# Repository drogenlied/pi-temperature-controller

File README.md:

# Pi temperature controller
A Raspberry Pi based H-bridge controller designed to stabilize temperatures in an optics lab

## Hardware
  * Raspberry Pi (Model 2 recommended)
  * Measurement Specialities TSYS01 temperature sensor
  * Adum 14xx isolators between control and driver
  * VNH3SP30 H-bridge driver for output
  
## Features
  * Can control Peltier elements as well as resistive heaters for temperature stabilisation.
  * Fabrication should be possible in every university PCB shop
  * Hand soldering is possible but reflowing the VNH3SP30 is recommended
  
## Software
Test software is in this repository but https://github.com/Ulm-IQO/qudi is recommended for operation.

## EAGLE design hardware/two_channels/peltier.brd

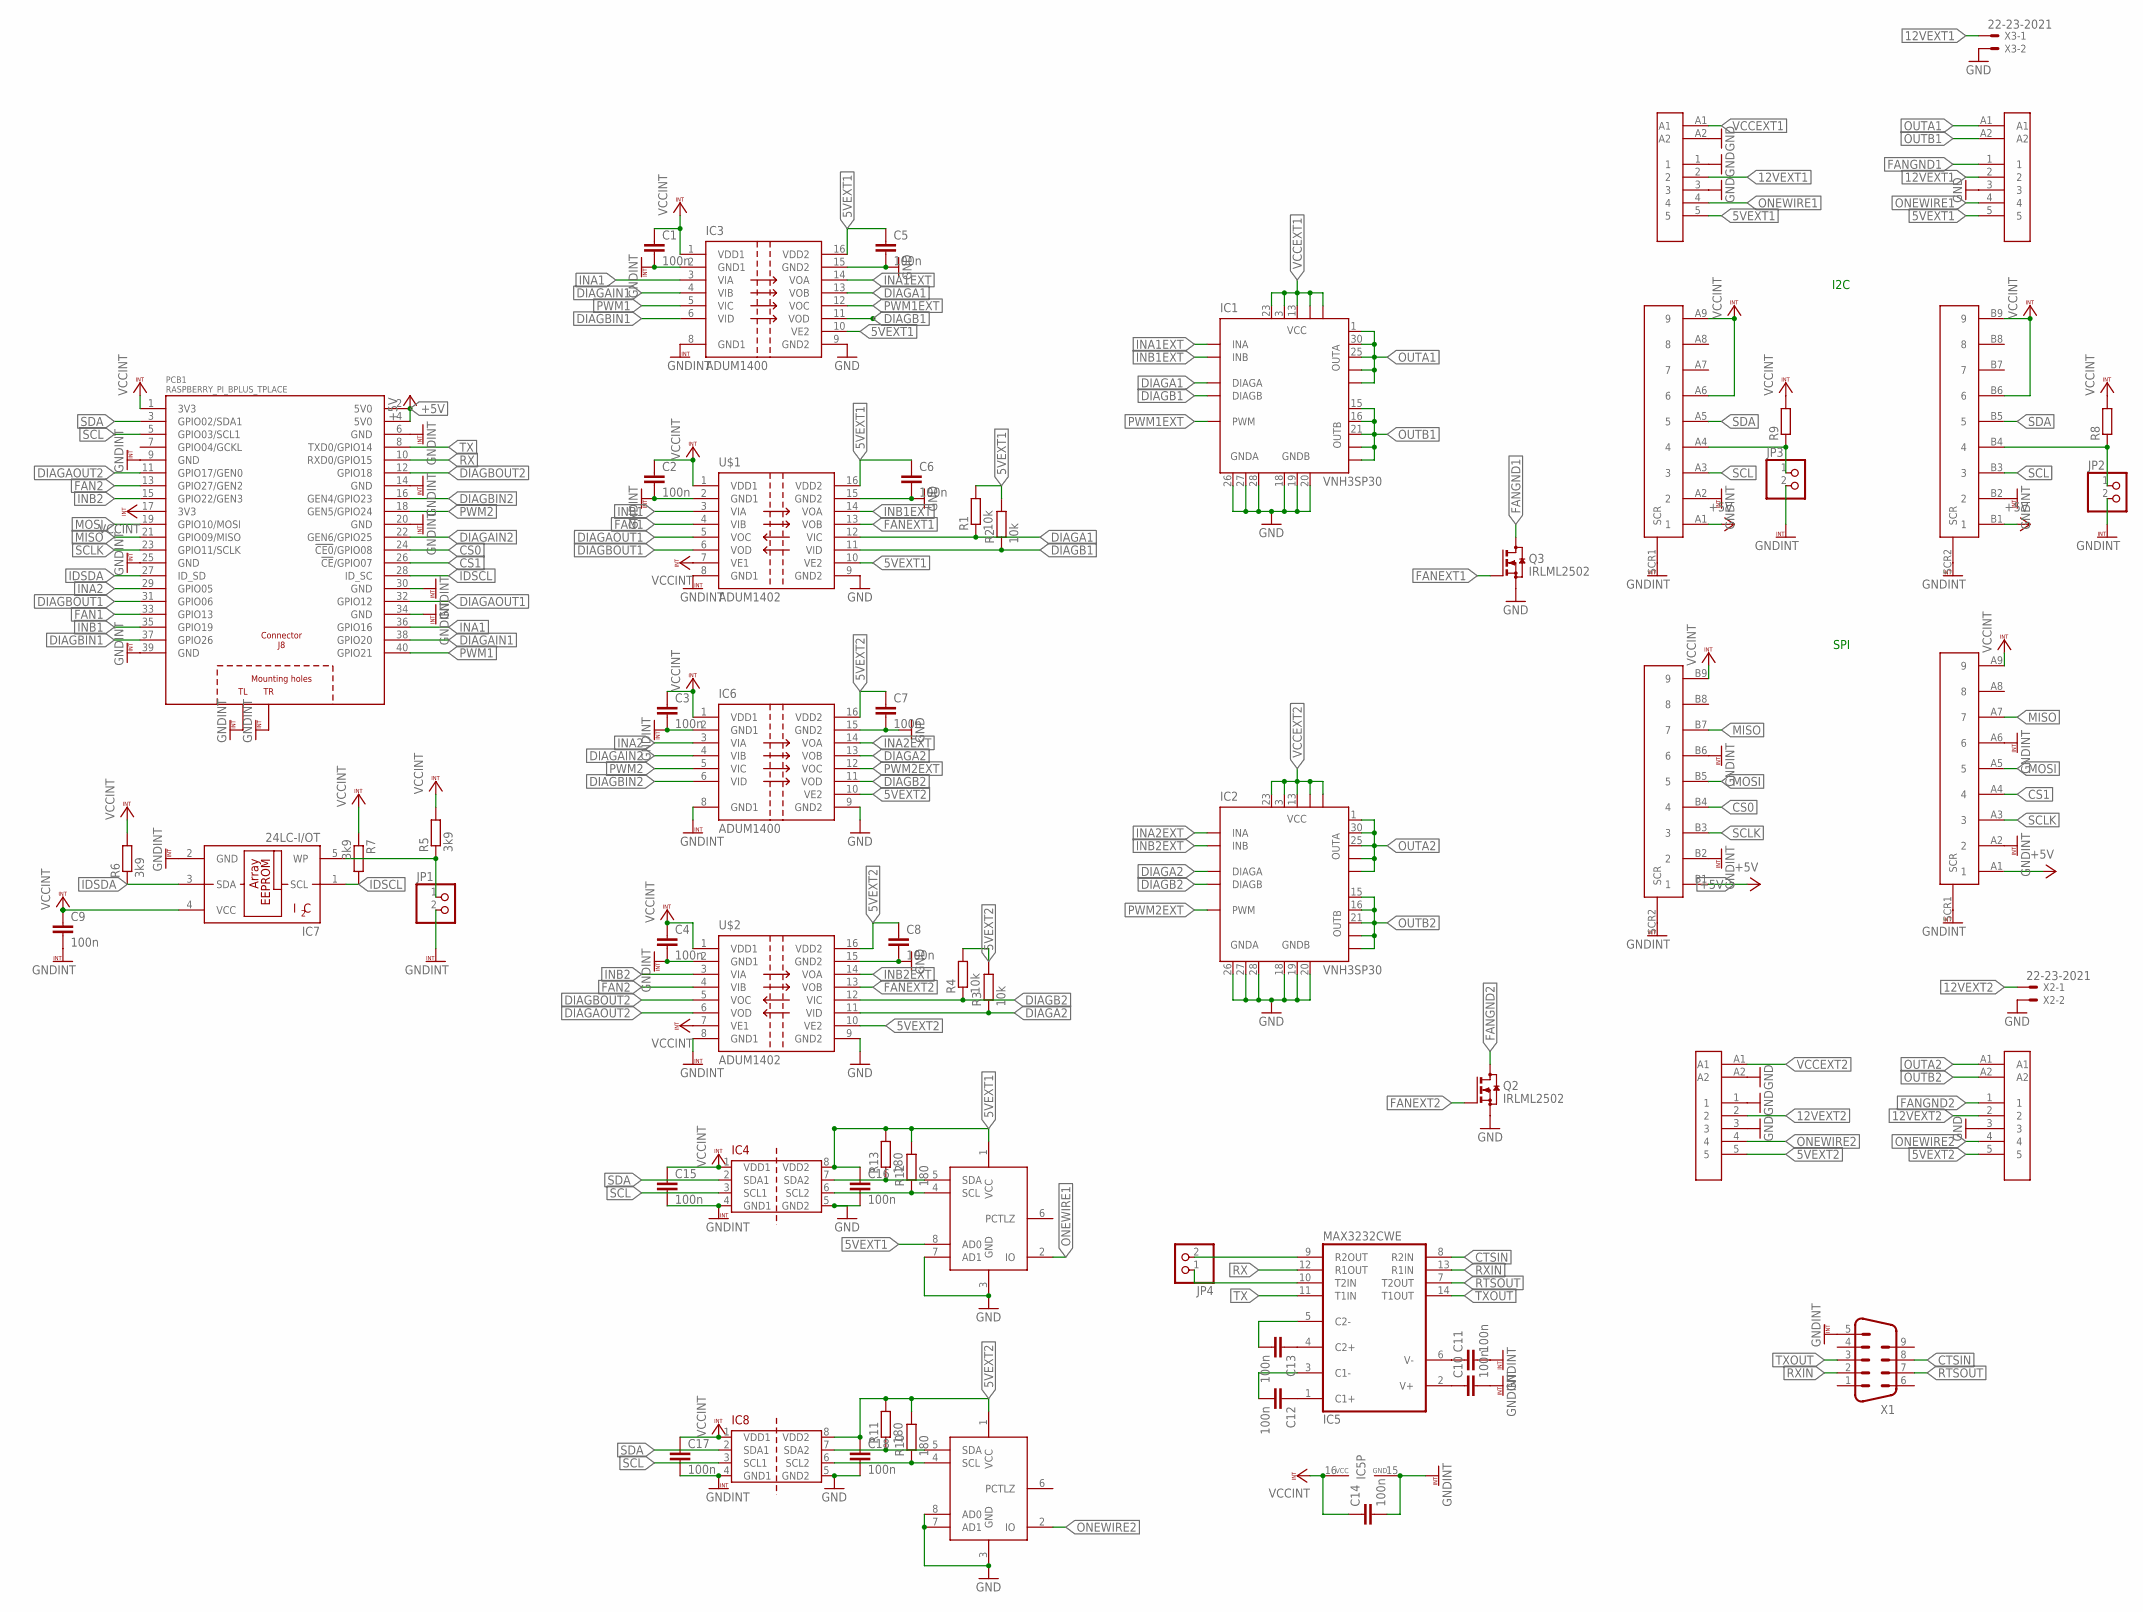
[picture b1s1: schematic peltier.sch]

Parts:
C1, C2, C3, C4, C5, C6, C7, C8, C9, C10, C11, C12, C13, C14, C15, C16, C17, C18: 100n; C0805
IC1, IC2: VNH3SP30; MULTIPOWERSO-30
IC3, IC6: ADUM1400; SO16W
IC4, IC8: ADUM1250; SO08
IC5: MAX3232CWE; SO16L
IC7: 24LC-I/OT; SOT23-5
JP1, JP2, JP3, JP4: PINHD-1X2; 1X02
PCB1: RASPBERRY_PI_BPLUS_TPLACE
Q2, Q3: IRLML2502; SOT23
R1, R2, R3, R4: 10k; R0805
R5, R6, R7: 3k9; R0805
R8, R9: R-EU_R0805; R0805
R10, R11, R12, R13: 180; R0805
U$1, U$2: ADUM1402; SO16W
U$3, U$4: 7W2-F
U$5, U$6: 7W2-M
U$11, U$12: 164A19919X
U$14, U$15: DS2483-100; SO-08
X1: M09HP
X2, X3: 22-23-2021

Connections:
5VEXT1: C5.1, C6.1, C16.1, IC3.10 (VE2), IC3.16 (VDD2), IC4.8 (VDD2), R1.2, R2.2, R12.2, R13.2, U$1.10 (VE2), U$1.16 (VDD2), U$3.5, U$5.5, U$14.1 (VCC), U$14.8 (AD0)
5VEXT2: C7.1, C8.1, C18.1, IC6.10 (VE2), IC6.16 (VDD2), IC8.8 (VDD2), R3.2, R4.2, R10.2, R11.2, U$2.10 (VE2), U$2.16 (VDD2), U$4.5, U$6.5, U$15.1 (VCC)
12VEXT1: U$3.2, U$5.2, X3.1
12VEXT2: U$4.2, U$6.2, X2.1
+5V: PCB1.2 (5V0), PCB1.4 (5V0), U$11.A1 (1), U$11.B1 (1), U$12.A1 (1), U$12.B1 (1)
CS0: PCB1.24 (!CE0!/GPIO08), U$12.B4 (4)
CS1: PCB1.26 (!CE!/GPIO07), U$12.A4 (4)
CTSIN: IC5.8 (R2IN), X1.8
DIAGA1: IC1.6 (DIAGA), IC3.13 (VOB), R1.1, U$1.12 (VIC)
DIAGA2: IC2.6 (DIAGA), IC6.13 (VOB), R3.1, U$2.11 (VID)
DIAGAIN1: IC3.4 (VIB), PCB1.38 (GPIO20)
DIAGAIN2: IC6.4 (VIB), PCB1.22 (GEN6/GPIO25)
DIAGAOUT1: PCB1.32 (GPIO12), U$1.5 (VOC)
DIAGAOUT2: PCB1.11 (GPIO17/GEN0), U$2.6 (VOD)
DIAGB1: IC1.10 (DIAGB), IC3.11 (VOD), R2.1, U$1.11 (VID)
DIAGB2: IC2.10 (DIAGB), IC6.11 (VOD), R4.1, U$2.12 (VIC)
DIAGBIN1: IC3.6 (VID), PCB1.37 (GPIO26)
DIAGBIN2: IC6.6 (VID), PCB1.16 (GEN4/GPIO23)
DIAGBOUT1: PCB1.31 (GPIO06), U$1.6 (VOD)
DIAGBOUT2: PCB1.12 (GPIO18), U$2.5 (VOC)
FAN1: PCB1.33 (GPIO13), U$1.4 (VIB)
FAN2: PCB1.13 (GPIO27/GEN2), U$2.4 (VIB)
FANEXT1: Q3.1 (G), U$1.13 (VOB)
FANEXT2: Q2.1 (G), U$2.13 (VOB)
FANGND1: Q3.3 (D), U$3.1
FANGND2: Q2.3 (D), U$4.1
GND: C5.2, C6.2, C7.2, C8.2, C16.2, C18.2, IC1.18 (GNDB), IC1.19 (GNDB), IC1.20 (GNDB), IC1.26 (GNDA), IC1.27 (GNDA), IC1.28 (GNDA), IC2.18 (GNDB), IC2.19 (GNDB), IC2.20 (GNDB), IC2.26 (GNDA), IC2.27 (GNDA), IC2.28 (GNDA), IC3.9 (GND2), IC3.15 (GND2), IC4.5 (GND2), IC6.9 (GND2), IC6.15 (GND2), IC8.5 (GND2), Q2.2 (S), Q3.2 (S), U$1.9 (GND2), U$1.15 (GND2), U$2.9 (GND2), U$2.15 (GND2), U$3.3, U$4.3, U$5.1, U$5.3, U$5.A2, U$6.1, U$6.3, U$6.A2, U$14.3 (GND), U$14.7 (AD1), U$15.3 (GND), U$15.7 (AD1), U$15.8 (AD0), X2.2, X3.2
GNDINT: C1.2, C2.2, C3.2, C4.2, C9.2, C10.2, C11.2, C14.2, C15.2, C17.2, IC3.2 (GND1), IC3.8 (GND1), IC4.4 (GND1), IC5.15 (GND), IC6.2 (GND1), IC6.8 (GND1), IC7.2 (GND), IC8.4 (GND1), JP1.2, JP2.2, JP3.2, PCB1.6 (GND), PCB1.9 (GND), PCB1.14 (GND), PCB1.20 (GND), PCB1.25 (GND), PCB1.30 (GND), PCB1.34 (GND), PCB1.39 (GND), PCB1.PE_TL (TL), PCB1.PE_TR (TR), U$1.2 (GND1), U$1.8 (GND1), U$2.2 (GND1), U$2.8 (GND1), U$11.A2 (2), U$11.B2 (2), U$11.SCR1 (SCR), U$11.SCR2 (SCR), U$12.A2 (2), U$12.A6 (6), U$12.B2 (2), U$12.B6 (6), U$12.SCR1 (SCR), U$12.SCR2 (SCR), X1.5
IDSCL: IC7.1 (SCL), PCB1.28 (ID_SC), R7.2
IDSDA: IC7.3 (SDA), PCB1.27 (ID_SD), R6.1
INA1: IC3.3 (VIA), PCB1.36 (GPIO16)
INA1EXT: IC1.5 (INA), IC3.14 (VOA)
INA2: IC6.3 (VIA), PCB1.29 (GPIO05)
INA2EXT: IC2.5 (INA), IC6.14 (VOA)
INB1: PCB1.35 (GPIO19), U$1.3 (VIA)
INB1EXT: IC1.11 (INB), U$1.14 (VOA)
INB2: PCB1.15 (GPIO22/GEN3), U$2.3 (VIA)
INB2EXT: IC2.11 (INB), U$2.14 (VOA)
MISO: PCB1.21 (GPIO09/MISO), U$12.A7 (7), U$12.B7 (7)
MOSI: PCB1.19 (GPIO10/MOSI), U$12.A5 (5), U$12.B5 (5)
unnamed: IC7.5 (WP), JP1.1, R5.1
unnamed: JP3.1, R9.1, U$11.A4 (4)
unnamed: JP2.1, R8.1, U$11.B4 (4)
unnamed: C10.1, IC5.2 (V+)
unnamed: C11.1, IC5.6 (V-)
unnamed: C12.1, IC5.1 (C1+)
unnamed: C12.2, IC5.3 (C1-)
unnamed: C13.1, IC5.4 (C2+)
unnamed: C13.2, IC5.5 (C2-)
unnamed: IC5.9 (R2OUT), JP4.2
unnamed: IC5.10 (T2IN), JP4.1
unnamed: IC4.7 (SDA2), R13.1, U$14.5 (SDA)
unnamed: IC4.6 (SCL2), R12.1, U$14.4 (SCL)
unnamed: IC8.7 (SDA2), R11.1, U$15.5 (SDA)
unnamed: IC8.6 (SCL2), R10.1, U$15.4 (SCL)
ONEWIRE1: U$3.4, U$5.4, U$14.2 (IO)
ONEWIRE2: U$4.4, U$6.4, U$15.2 (IO)
OUTA1: IC1.1 (OUTA), IC1.25 (OUTA), IC1.30 (OUTA), IC1.OUTA, IC1.OUTA@1 (OUTA), U$3.A1
OUTA2: IC2.1 (OUTA), IC2.25 (OUTA), IC2.30 (OUTA), IC2.OUTA, IC2.OUTA@1 (OUTA), U$4.A1
OUTB1: IC1.15 (OUTB), IC1.16 (OUTB), IC1.21 (OUTB), IC1.OUTB, IC1.OUTB@1 (OUTB), U$3.A2
OUTB2: IC2.15 (OUTB), IC2.16 (OUTB), IC2.21 (OUTB), IC2.OUTB, IC2.OUTB@1 (OUTB), U$4.A2
PWM1: IC3.5 (VIC), PCB1.40 (GPIO21)
PWM1EXT: IC1.8 (PWM), IC3.12 (VOC)
PWM2: IC6.5 (VIC), PCB1.18 (GEN5/GPIO24)
PWM2EXT: IC2.8 (PWM), IC6.12 (VOC)
RTSOUT: IC5.7 (T2OUT), X1.7
RX: IC5.12 (R1OUT), PCB1.10 (RXD0/GPIO15)
RXIN: IC5.13 (R1IN), X1.2
SCL: IC4.3 (SCL1), IC8.3 (SCL1), PCB1.5 (GPIO03/SCL1), U$11.A3 (3), U$11.B3 (3)
SCLK: PCB1.23 (GPIO11/SCLK), U$12.A3 (3), U$12.B3 (3)
SDA: IC4.2 (SDA1), IC8.2 (SDA1), PCB1.3 (GPIO02/SDA1), U$11.A5 (5), U$11.B5 (5)
TX: IC5.11 (T1IN), PCB1.8 (TXD0/GPIO14)
TXOUT: IC5.14 (T1OUT), X1.3
VCCEXT1: IC1.3 (VCC), IC1.13 (VCC), IC1.23 (VCC), IC1.VCC, IC1.VCC@1 (VCC), U$5.A1
VCCEXT2: IC2.3 (VCC), IC2.13 (VCC), IC2.23 (VCC), IC2.VCC, IC2.VCC@1 (VCC), U$6.A1
VCCINT: C1.1, C2.1, C3.1, C4.1, C9.1, C14.1, C15.1, C17.1, IC3.1 (VDD1), IC4.1 (VDD1), IC5.16 (VCC), IC6.1 (VDD1), IC7.4 (VCC), IC8.1 (VDD1), PCB1.1 (3V3), PCB1.17 (3V3), R5.2, R6.2, R7.1, R8.2, R9.2, U$1.1 (VDD1), U$1.7 (VE1), U$2.1 (VDD1), U$2.7 (VE1), U$11.A6 (6), U$11.A9 (9), U$11.B6 (6), U$11.B9 (9), U$12.A9 (9), U$12.B9 (9)

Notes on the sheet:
I2C
SPI

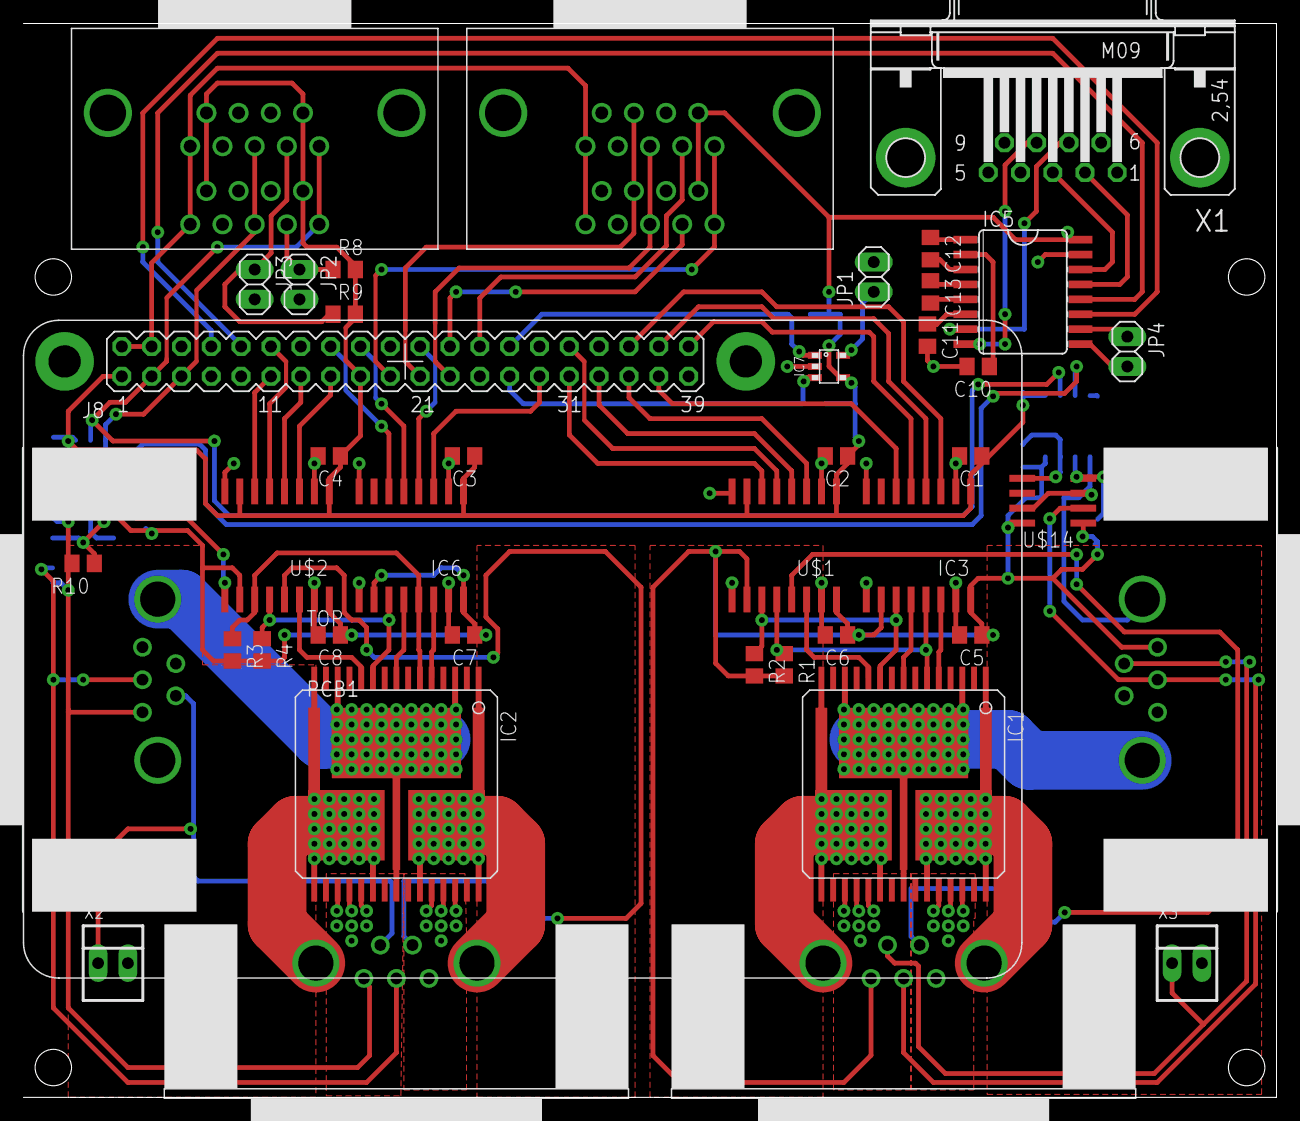
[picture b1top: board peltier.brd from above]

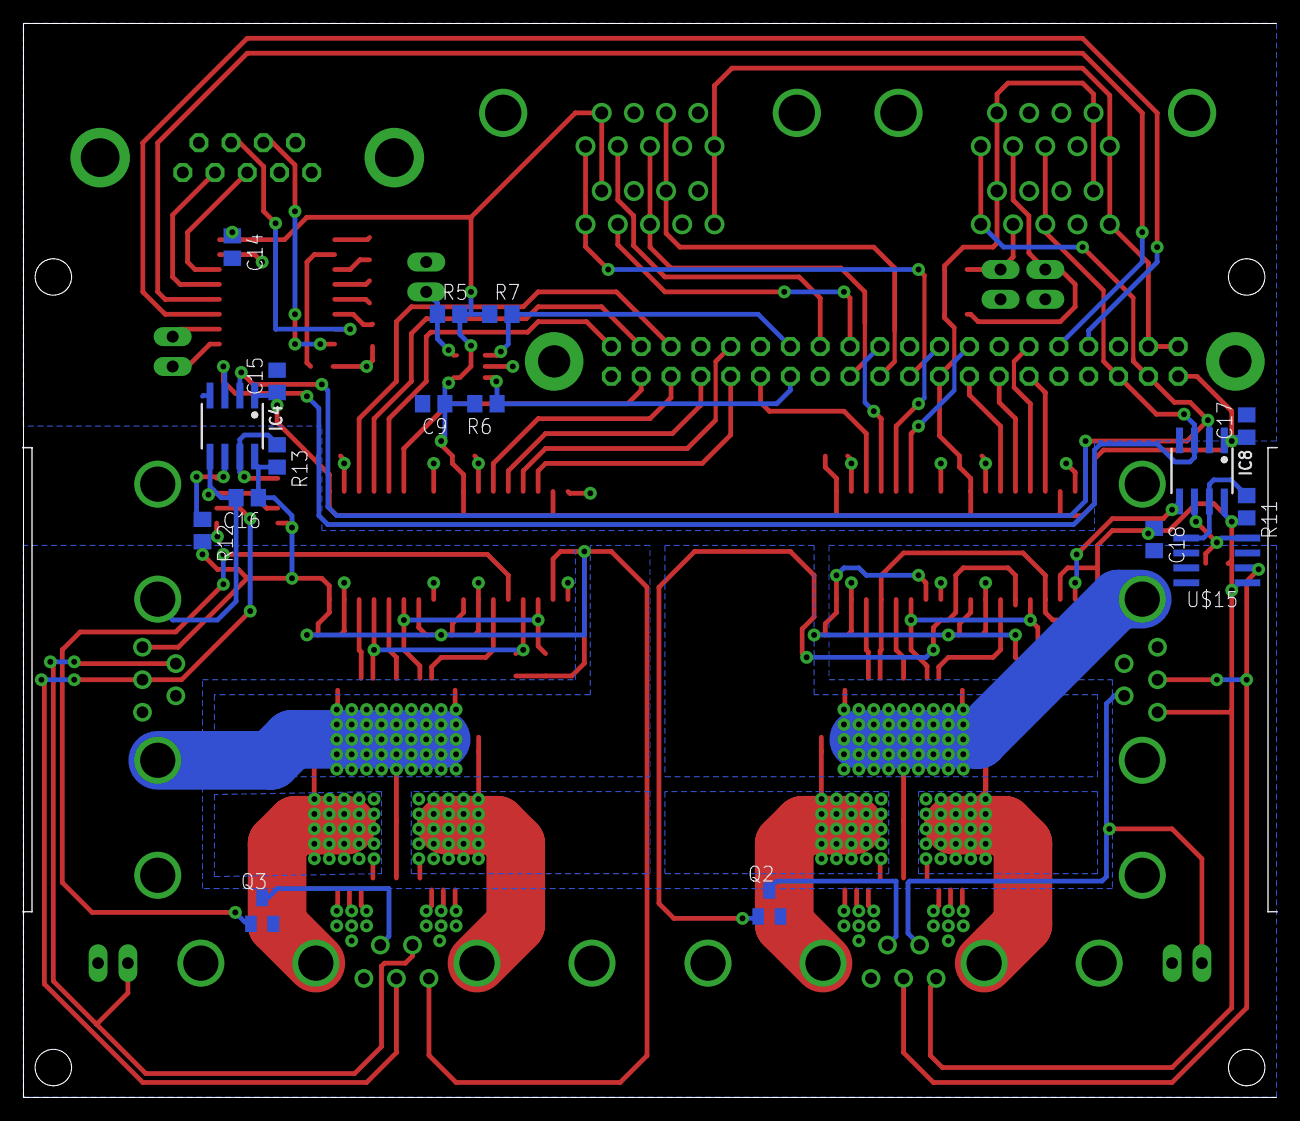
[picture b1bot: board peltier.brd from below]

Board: 2 copper layers, 106.7 x 91.4 mm, 59 parts (17 on the bottom side), 76 nets.

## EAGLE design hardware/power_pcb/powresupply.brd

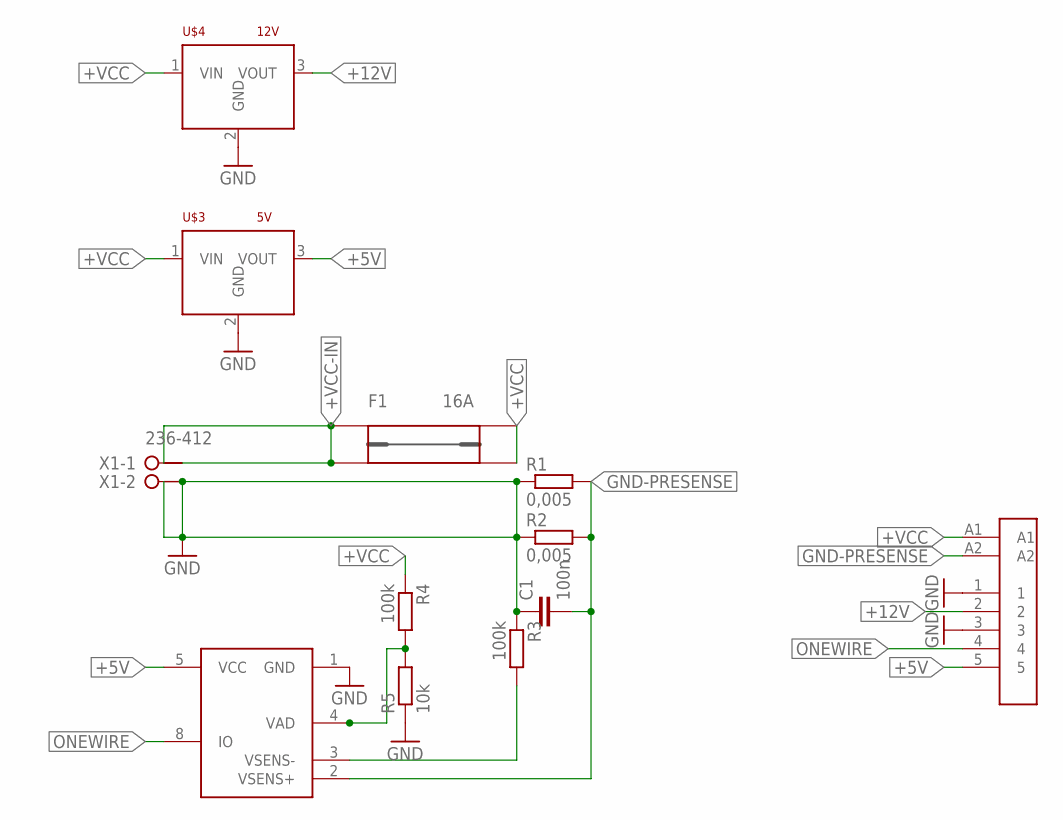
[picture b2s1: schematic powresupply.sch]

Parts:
C1: 100n; C0805
F1: 16A; 1A3400
R1, R2: 0,005; R2512
R3, R4: 100k; R0805
R5: 10k; R0805
U$1: 7W2-F
U$2: DS2438; SO-08
U$3: 5V; RECOM
U$4: 12V; RECOM
X1: 236-412

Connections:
+5V: U$1.5, U$2.5 (VCC), U$3.3 (VOUT)
+12V: U$1.2, U$4.3 (VOUT)
+VCC: F1.P$3, F1.P$4, R4.1, U$1.A1, U$3.1 (VIN), U$4.1 (VIN)
+VCC-IN: F1.P$1, F1.P$2, X1.1@1 (KL1), X1.1@2 (KL2)
GND: C1.1, R1.1, R2.1, R3.1, R5.1, U$1.1, U$1.3, U$2.1 (GND), U$3.2 (GND), U$4.2 (GND), X1.2@1 (KL1), X1.2@2 (KL2)
GND-PRESENSE: C1.2, R1.2, R2.2, U$1.A2, U$2.2 (VSENS+)
unnamed: R4.2, R5.2, U$2.4 (VAD)
unnamed: R3.2, U$2.3 (VSENS-)
ONEWIRE: U$1.4, U$2.8 (IO)

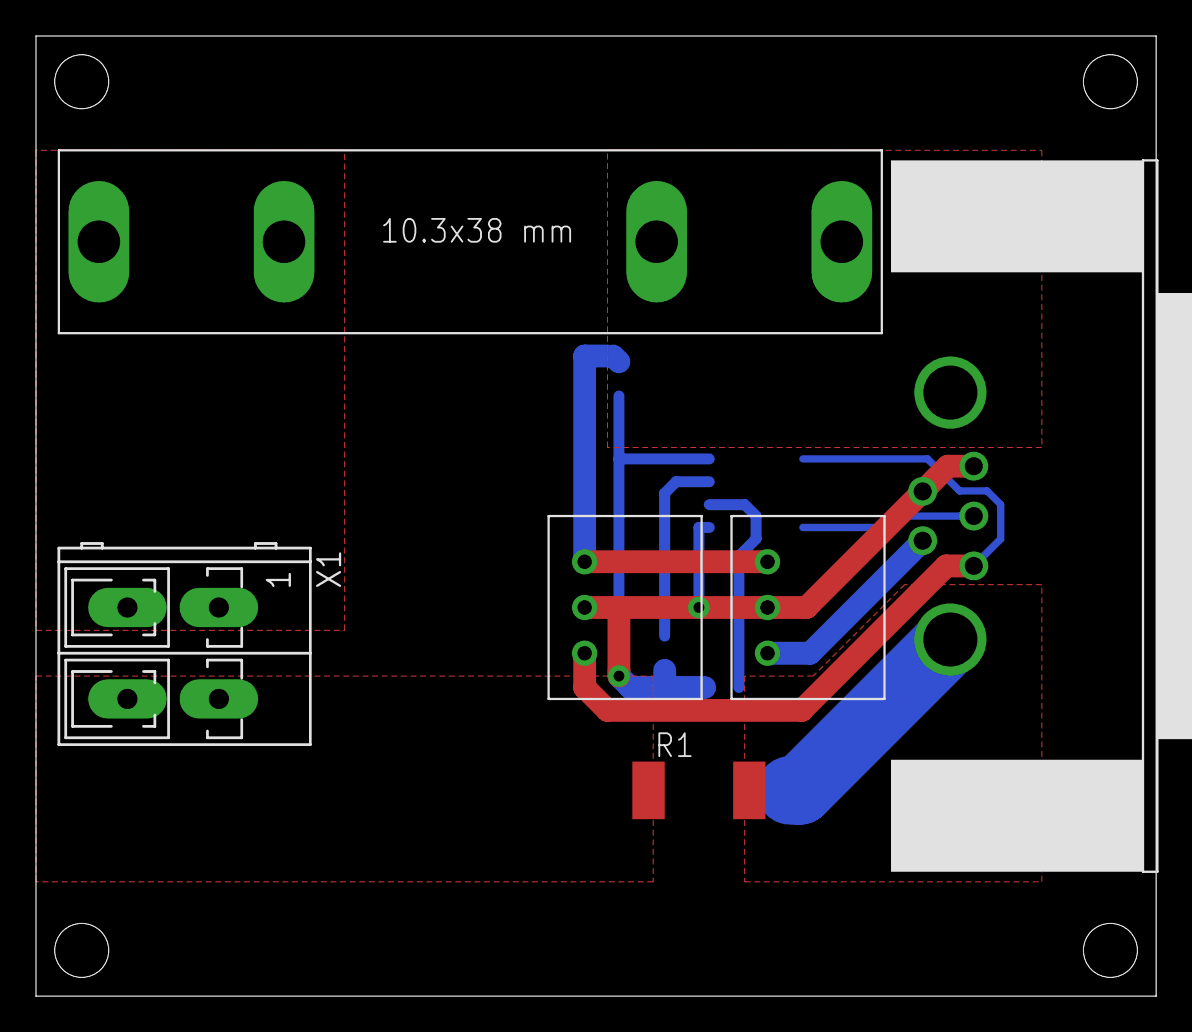
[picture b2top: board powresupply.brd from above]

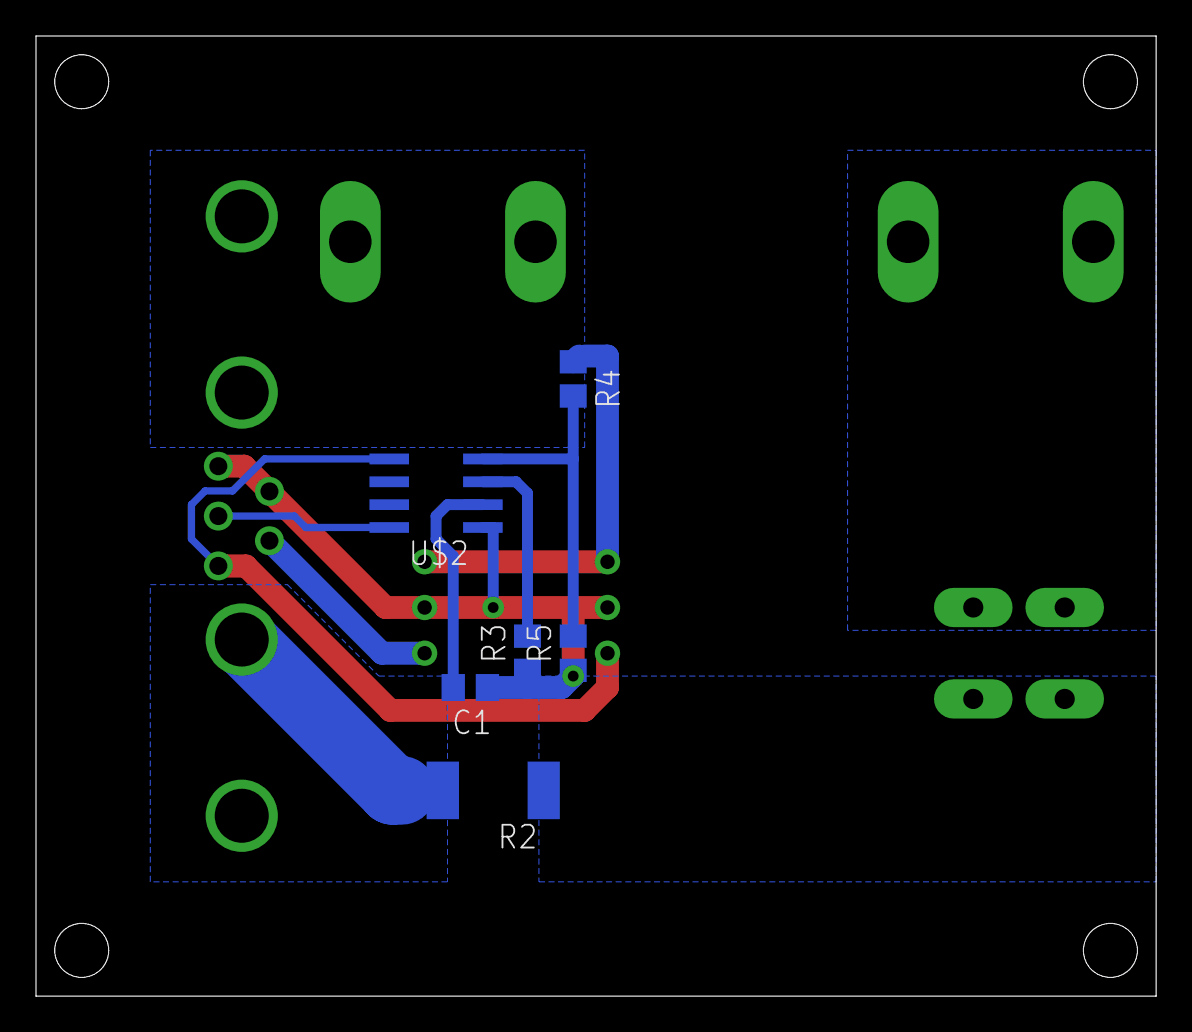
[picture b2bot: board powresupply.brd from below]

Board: 2 copper layers, 62.2 x 53.3 mm, 12 parts (6 on the bottom side), 9 nets.

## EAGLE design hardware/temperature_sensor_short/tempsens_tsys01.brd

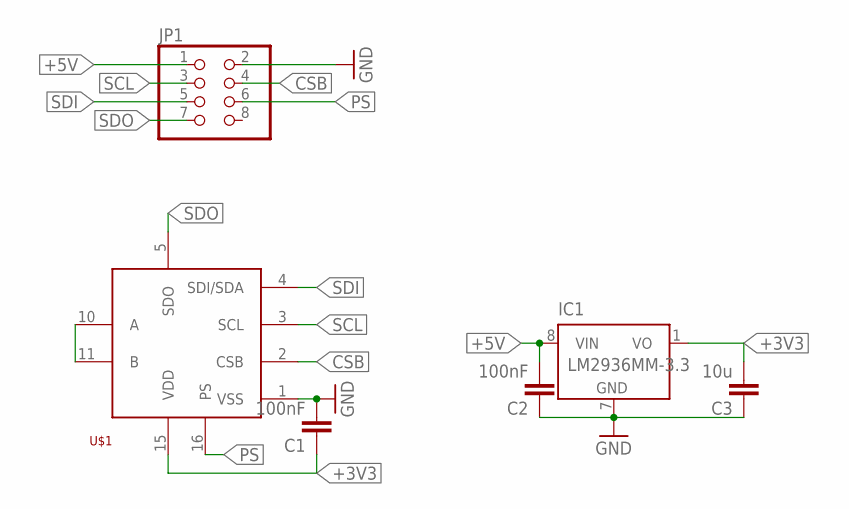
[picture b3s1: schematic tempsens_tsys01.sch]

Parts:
C1, C2: 100nF; C0603K
C3: 10u; C0805
IC1: LM2936MM-3.3; MINI-SO8
JP1: PINHD-2X4_2.00; 2X04M
U$1: TSYS01NOPAD; TSYS01_NOPAD

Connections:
+3V3: C1.1, C3.2, IC1.1 (VO), U$1.15 (VDD)
+5V: C2.2, IC1.8 (VIN), JP1.1
CSB: JP1.4, U$1.2 (CSB)
GND: C1.2, C2.1, C3.1, IC1.7 (GND), JP1.2, U$1.1 (VSS)
unnamed: U$1.10 (A), U$1.11 (B)
PS: JP1.6, U$1.16 (PS)
SCL: JP1.3, U$1.3 (SCL)
SDI: JP1.5, U$1.4 (SDI/SDA)
SDO: JP1.7, U$1.5 (SDO)

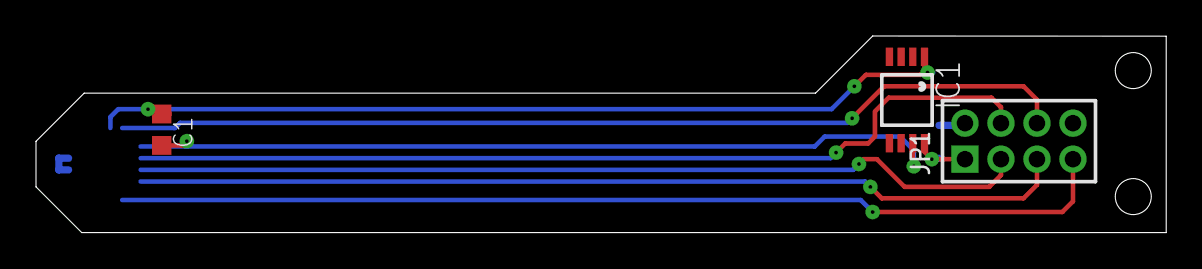
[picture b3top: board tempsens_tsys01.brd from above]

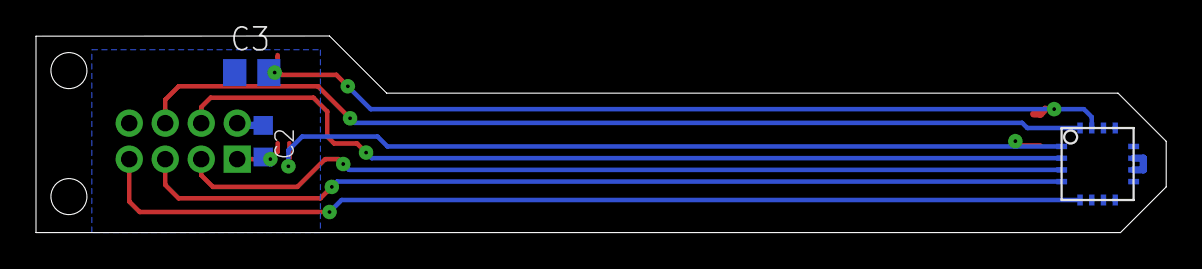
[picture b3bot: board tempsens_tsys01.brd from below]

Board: 2 copper layers, 62.8 x 10.9 mm, 6 parts (3 on the bottom side), 9 nets.

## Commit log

2016-07-06 raspberry pi hat eeprom files
2016-07-06 software controlling temperature sensors and power driver
2016-07-06 add hardware design for temperature controller project
2016-07-06 add license
